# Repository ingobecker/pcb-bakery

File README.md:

# SMD Reflow oven

I converted an old bread machine into a reflow oven. I replaced the original
control board with a STM32F103 bluepill board, a 2 chanel relay board as well
as a type k thermocouple.  The components for the conversion coast around 10€
in total and it should be possible to apply them to most bread machines,
electric BBQs, raclette grills etc.

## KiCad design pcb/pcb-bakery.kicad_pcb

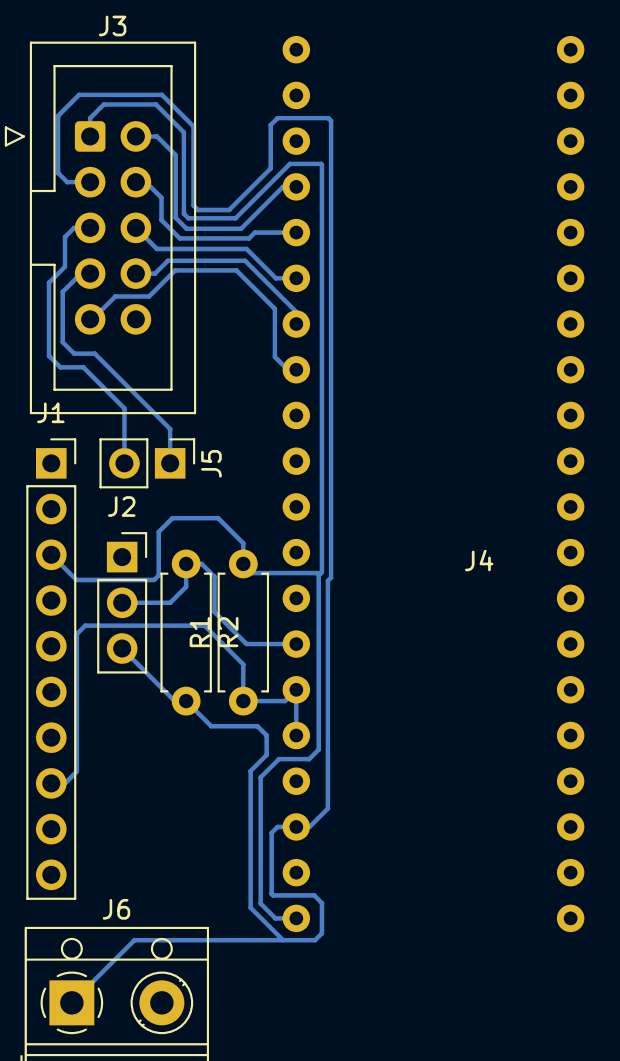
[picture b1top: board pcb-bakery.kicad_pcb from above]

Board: 2 copper layers, 8 parts (0 on the bottom side), 12 nets.

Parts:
J1: TEMP_SENSOR; PinSocket_1x10_P2.54mm_Vertical
J2: HEATER_RELAY; PinSocket_1x03_P2.54mm_Vertical
J3: FRONTPANEL; IDC-Header_2x05_P2.54mm_Vertical
J4: Bluepill
J5: SWD; PinHeader_1x02_P2.54mm_Vertical
J6: 5V DC; TerminalBlock_RND_205-00012_1x02_P5.00mm_Horizontal
R1: 4k7; R_Axial_DIN0207_L6.3mm_D2.5mm_P7.62mm_Horizontal
R2: 1k; R_Axial_DIN0207_L6.3mm_D2.5mm_P7.62mm_Horizontal

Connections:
+5V: J2.3, J3.3, J4.38, J6.1, R2.2
/BTN: J3.2, J4.24
/Heater: J2.2, J4.34, R2.1
/LED: J3.4, J4.25
/OneWire_Read: J1.8, J4.35, J4.36, R1.1
/RX1: J3.8, J4.27
/SWCLK: J3.5, J5.2
/SWDIO: J3.7, J5.1
/TX1: J3.6, J4.26
/USR: J3.9, J4.28
GND: J1.1, J2.1, J3.10, J4.19, J4.20, J4.39, J6.2
VCC: J1.3, J3.1, J4.18, J4.40, R1.2

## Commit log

2020-10-09 Add PCB
2020-10-09 Add Gemfile used by Containerfile
